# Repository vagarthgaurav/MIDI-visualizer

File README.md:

# MIDI Visualiser

by: Vagarth Gaurav and Maksim Eremenko

**Faculty of Technology and Bionics**

***Rhine-Waal University of Applied Sciences***

Date: 23 January 2024

----

## Abstract

The MIDI Visualiser implements an overarching idea of showing visual patterns on a rudimentary screen made of smart light-emitting diode (LED) strips based on the Musical Instrument Digital Interface (MIDI) keyboard output. The board design includes a buck-converter that steps down the power input voltage from 12v to 5v for the ATmega microcontroller unit (MCU), while also feeding the 12v to LED strips. MCU receives a MIDI input through a software serial, processes it and sends an output signal controlling an LED strip to display different patterns based on the pressed key. Out of curious ambition - prevalently SMD components were used, which ultimately led to a failed attempt to print at Hochschule Rhein-Waal (HSRW), instead the PCB was ordered from a third party. After arduous soldering, resoldering, coding and debugging the concept proved to be feasible. Although the prototype is working - further code optimization is necessary and additional ergonomic improvements should be considered.

## 1 Introduction

From the very dawn of Humankind our senses were the main gateway of perceiving and accepting the world around us. Throughout the social evolution of Homo sapiens, we've developed peculiar ways of stimulating our senses, ways that "make sense" only from a perspective of a conscious being with ears and sight. A marvelous play of stimulations to our hearing facilities that became known as music, and an intriguing play of visual symbols that found itself in different aspects of visual art and media. Consciously or not - our project stands among the attempts to unite and enhance an auditory sensation with a visual one.

At the end of the 20th century music entered the electronic era, synthesizers rose in popularity and MIDI was developed. Digital MIDI signals can be sent by any MIDI-compatibly musical instrument, such as keyboards, guitars and other more exotic contraptions. These signals contain information about the note being pressed or released, which can be processed by a 3rd party computing unit usually responsible for generating a corresponding sound, but in our case - responsible for generating visual patterns on an LED screen made of smart LED strips (further simply "LED screen").

LED screen therefore can dynamically respond to the notes being played, different animated patterns can be shown in different parts of the screen. Patterns can be colored and animated based on the press and release velocities creating an immersive supplementary experience to the music being played.

The following Chapter 2 presents our approach to implementing this idea, the hardware we designed and the software we wrote, as well as inevitable issues we've encountered.
Chapter 3 describes and illustrates the results, our success and our shortcomings. 
Finally, Chapter 4 will discuss the viability of our approach and potential improvements.

## 2	Methodology

### 2.1	Concept development

The initial concept was outlined in the following diagram:

A block diagram of an initial idea.

The following MIDI schematic depicts MIDI input and throughput isolated from the process control block (PCB) circuit via an opto-coupler.

Isolated MIDI IN and THRU.
(C) 1985 MIDI Manufacturers Association via https://diyaudiocircuits.com/midi-buffer/

Additionally, we already had a 12V 5A power source in our possession, so it was decided to design the solution around that power input.

From these, an idea of core circuit elements crystallized:
- A voltage regulator that can efficiently step down from 12V to 5V.
- MIDI input and throughput isolated from the circuit by means of an optocoupler.
- 5V ATmega328p MCU to read and interpret incoming MIDI signal.
- LED screen made of 3 rows of smart LED strips powered by 12V line.
- Performant software to bind MIDI input with visual LED screen output.
- Programmer pins
- Pins for power and auxiliary switches

### 2.2	Circuit design

The circuit was designed in KiCad

SMD components were selected wherever possible for their compact size and as a personal opportunity to discover SMD PCB manufacturing process.
As a voltage regulator - a buck convertor was used due to its high efficiency in comparison to archaic linear voltage regulators.

#### 2.2.1 Power regulator

Power regulator circuit

The device uses a buck converter to convert 12V to 5V necessary to power the MCU and other IC’s. The device used is ADP2303ARDZ-5.0 from Analog Devices. The circuit was designed in accordance with the typical application circuit from the datasheet. [1] 

#### 2.2.2 Microcontroller and crytal circuitry

Microcontroller and crystal circuitry

The microcontroller chosen is an ATmega328p-au. As datasheet 2 suggests the MCU requires a 16Mhz clock crystal. The MCU has associated decoupling capacitors of 1uF and a bulk decoupling capacitor of 10uF. The MIDI input signal is read in by the MCU at Pin PD5. The output for the LED data pin is assigned to Pin PB0. 

Prior to soldering the IC to the PCB the Arduino bootloader was uploaded with the use of a TQFP32 breakout board. This was necessary as an error in design was made by not including an ISP header for programming. The Arduino bootloader can only be uploaded with the MCU’s ISP pins. 

The program is uploaded to the PCB once it is completed with the help of an FTDI programmer. The PCB has pins broken out for plugging a programmer. 

#### 2.2.3 MIDI input

MIDI Input circuit

The MIDI signal is read in with the use of a MIDI socket. The signal is fed into an optocoupler for galvanic isolation to prevent ground loops. The signal then goes to the MCU for processing. 

#### 2.2.4 MIDI Thru

MIDI thru circuit

The MIDI thru circuit is fairly simple. A hex inverter IC is used with the signal passed through 2 inverters. This acts as a buffer for delivering a stable signal. 

### 2.3	Prototyping

The MIDI input circuitry was prototyped with a breadboard for a proof of concept. The circuit is the exact same as in the schematic with THT components. As expected the MIDI signal was successfully read. An Arduino Uno was used to read and process the signal. 

The power regulator circuit was also to be prototyped but unfortnately the ADP2303 is not available in a THT package and was therefore not possible. Nonetheless, since the Datasheet was very thorough and was implemented exactly according to specification this turned out to not be necessary after all. The power regulator in the final PCB outputs a steady 5V output as expected. 

### 2.4	Printing

The first attempt to print the KiCad design was made using HSRW electronics lab chemical PCB etching facilities.

Unfortunately, but not unexpectedly, due to the small width of SMD pads and traces (under 0.5mm) too many of the traces got destroyed during the etching process. As a result, it was decided to order an etched PCB from a 3rd party. Fortunately this time we received a perfect PCB that didn't require any manual alteration, so we were able to start the component soldering process.

### 2.5 Soldering

The soldering pipeline used involved a careful application of a limited amount of soldering paste to component pads using a soldering paste pump, followed by precise placement of SMD components using the magnetic pick-and-place machine. Afterwards, PCB was placed in a reflow oven which melted the paste effectively soldering the components in place. An initial attempt was not ideal, MCU came out of the oven with multiple pins short-circuited with melted solder. A cleanup attempt employing a soldering iron and a solder braid succeeded only partially. It was decided to desolder the MCU using the heat gun in the process of which the first PCB was destroyed.

PCB soldering was started from scratch using a fresh PCB and a new set of components, the same process was repeated, yet the second bake resulted in a resounding success with no short-circuits.

Following that thru-hole components (THC), such as MIDI ports, power jack and connector pins - were soldered. Subsequent connectivity tests showed that hardware functions as expected and opened a road ahead to software development and testing.

### 2.6 Software

Software was written using Arduino IDE as well as Visual Studio Code with an Arduino plugin.
The core idea behind the software was inspired by a style of image rendering employed by graphics processing unit (GPU) shaders. The software implements multiple crucial concepts:
- A screen, where every pixel is an LED addressable by an x and y coordinate.
- A shape that can have a specific size, position and color.
- A screen pixel that can sample every existing shape to determine its own color, potentially as a blend of colors of intersecting shapes.

The following libraries were used:

```c++
#include <MIDI.h>
#include <Adafruit_NeoPixel.h>
#include <Deneyap_RenkDonusturme.h>
```

Every main loop iteration - each screen pixel attempts to sample every existing shape, mix the colors of all the shapes it belong to (if any) and based on that conclude its own color:

```c++
Color pixelBrain(const AbsPosition &absPos, const RelPosition &relPos)
{    
    Color color = {0, 0, 0, 0};
    bool nocolor = true;

    // Loop through all the shape and sample every shape color. Returns 0 color if pixel doesnt belong to a shape.
    for (auto &shape : shapes)
    {
        if (shape.isActive())
        {
            // Sample color and mix it with a previously sampled color using alpha-blending
            auto c = shape.sampleColor(relPos);
            if (c.a != 0)
            {
                if (nocolor)
                {
                    color = c;
                    nocolor = false;
                }
                else
                {
                    color.a = lerp(color.a, 255, byteToFloat(c.a));
                }
            }
        }
    }

    // Return pixel color
    return color;
}
```

At the same time, MIDI input is listened to and in the event of a key press or release - a new shape is created or removed based on the note value in a way that leftmost keys generate shapes in the leftmost part of the screen, while rightmost - in the rightmost. The shape was meant to quickly fade in and gradually fade out when the key is released, although this approach was later altered.

The downside of this approach: each main loop iteration at worse does 3600 pixel iterations (60 pixels x 30 objects), initial assumption that MCU should be able to handle it at 120Hz of the main loop refresh rate - prooved to be false. At the full load, a significant slowdown is noticeable.

Additionally - the research suggests that limitations of ATmega memory make dynamic memory management highly undesirable due to possible rapid memory fragmentation leading to an inevitable silent crash. In response to that - everything, including shape instances, was preallocated, but due to the limited amount of memory (2kb) the hard limit of 30 simultaneous shapes on the screen was introduced.

Throughout the implementation testing, it became obvious that some of the MIDI events are simply missing. Through the following process of research and debugging it was discovered that the culprit might've been an initial ignorant decision to use a software serial pin instead of the hardware serial one, it appears that in a former case, some serial signals can be lost when MCU is busy with other work. 
If a shape disappearance depends on a MIDI note-off signal - then if such signal went missing - the shape will linger, which is visually noticeable and undoubtedly undesirable. Since we had no ability to reroute the MIDI trace to a hardware serial pin - the issue was worked around on the software side by listening only to note-on events that spawn the shape and fading out the shape after a set amount of time, this way it was possible to trade noticeable false positives for less noticeable false negatives.

## 5	Results

The final assembled PCB worked as intended. Uploading code with the FTDI programmer was successful. The MIDI signal was successfully read and processed by the MCU and the LED strip was illuminated with the correct animation. 

The only flaw in the design was the absence of an ISP header pins. This was crucial as the Arduino bootloader could not be installed on the MCU. As explained above an attempt was made to desolder the IC and to use a TQFP32 breakout board and to upload the bootloader. Unfortunately, the PCB and the MCU were damaged and had to start over with a fresh PCB.

The second attempt was successful and the PCB performed as intended.

The final PCB

## 6	Discussion

The goal of this project was to bring up a PCB that could decode a MIDI signal from an instrument and be able to play an animation on a Neopixel LED display. With this in mind, the project was a success. 

A few things that could have been optimized. The first being the use of Hardware serial instead of Software Serial. The software does not have sufficient speed and in consequence, dropped some of the MIDI messages. This could have been avoided by using Hardware Serial. Unfortunately, the Atmega328p-au has only one Serial port, which was already used for programming. Secondly, the code could have been optimized a lot. The current code unfortunately does not perform very well on the Atmega328p. The idea was for the code to be as robust as possible to be able to handle an LED display of any length. This proved to be too much for the MCU to handle. Code optimisation can improve the usability a lot. The third and final room for improvement is to upgrade the MCU entirely and use something that is faster and has a lot more RAM. An STM32 chip would be a massive improvement. An added benefit is more number of Serial ports. 

A comment on the issue of not including a ISP programming header as already mentioned before. The absence of which was a major downside, which was eventually solved but would have saved a lot of time and effort and would have added robustness to the board. In future designs the inclusion of ISP headers as well as a hardware debug port such as Serial wire debug would provide for a much more comfortable experience. 

The design was able to achieve all the requirements and functioned with only minor deficiencies that are easily fixable in a future iteration. 

Finally, the cost of the PCB was below the estimated €20 limit. Using only minimal components and allocating more budget to the most important parts worked out to a board that is capable of enhancing the music playing experience for less than €20. 

## 7	Concluding Comments

A future iteration of this design would certainly include the above-mentioned improvements as well as a few more user experience-enhancing aspects. A 3D printable case to fit the board would help in protecting the board. An Onboard LED array would be an added benefit that could make the device function independently without the need for an external LED strip display. A seamless switching between the onboard and external display by detecting if a display is plugged in would make the device a well-rounded product. 

It's also undoubtedly possible to refactor the code to drastically reduce the amount of per-loop iterations by iterating over the shapes and filling pixels, instead of iterating over pixels and sampling shapes. This approach will not result in any perceivable drawbacks, except of an arguable drawback of worse code architecture, but will most likely significantly increase performance.

The experience of going through the project was very enjoyable and rewarding. The opportunity to learn was immense and the knowledge gained from this can be certainly applied to future projects.

## 8	References

* [1] ADP2303 Datasheet - https://www.analog.com/media/en/technical-documentation/data-sheets/adp2302_2303.pdf
* [2] ATmega328p-au datasheet - https://www.mouser.de/datasheet/2/268/ATmega48A_PA_88A_PA_168A_PA_328_P_DS_DS40002061B-3050139.pdf

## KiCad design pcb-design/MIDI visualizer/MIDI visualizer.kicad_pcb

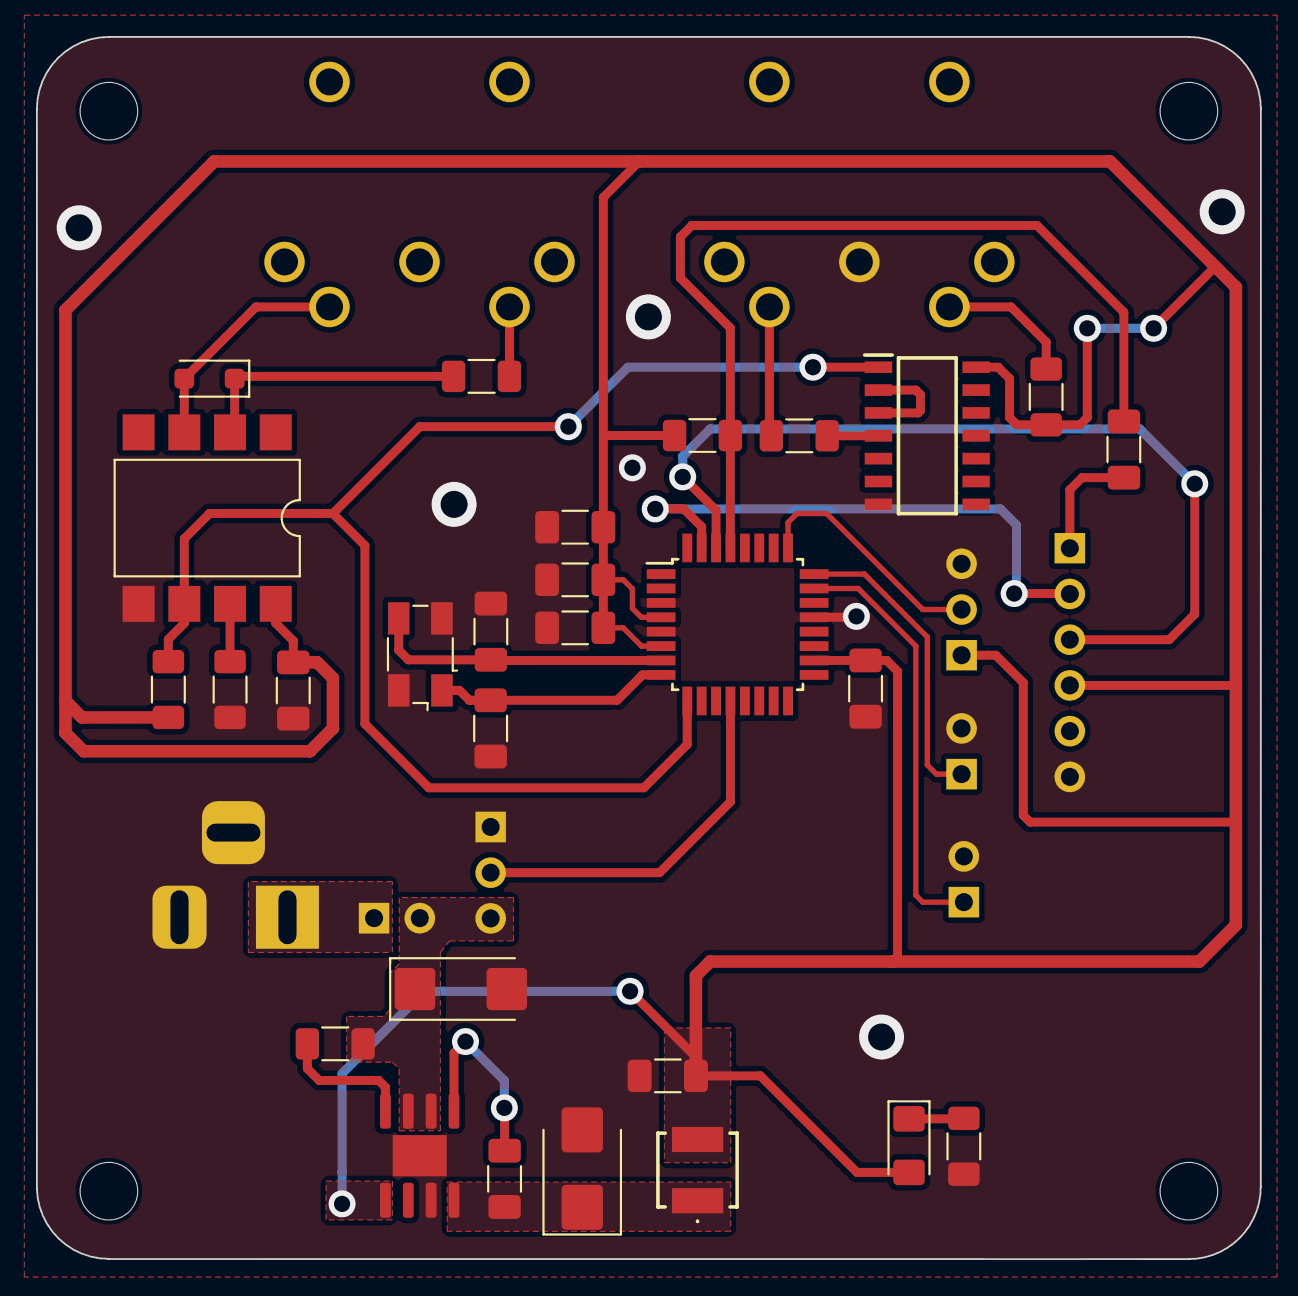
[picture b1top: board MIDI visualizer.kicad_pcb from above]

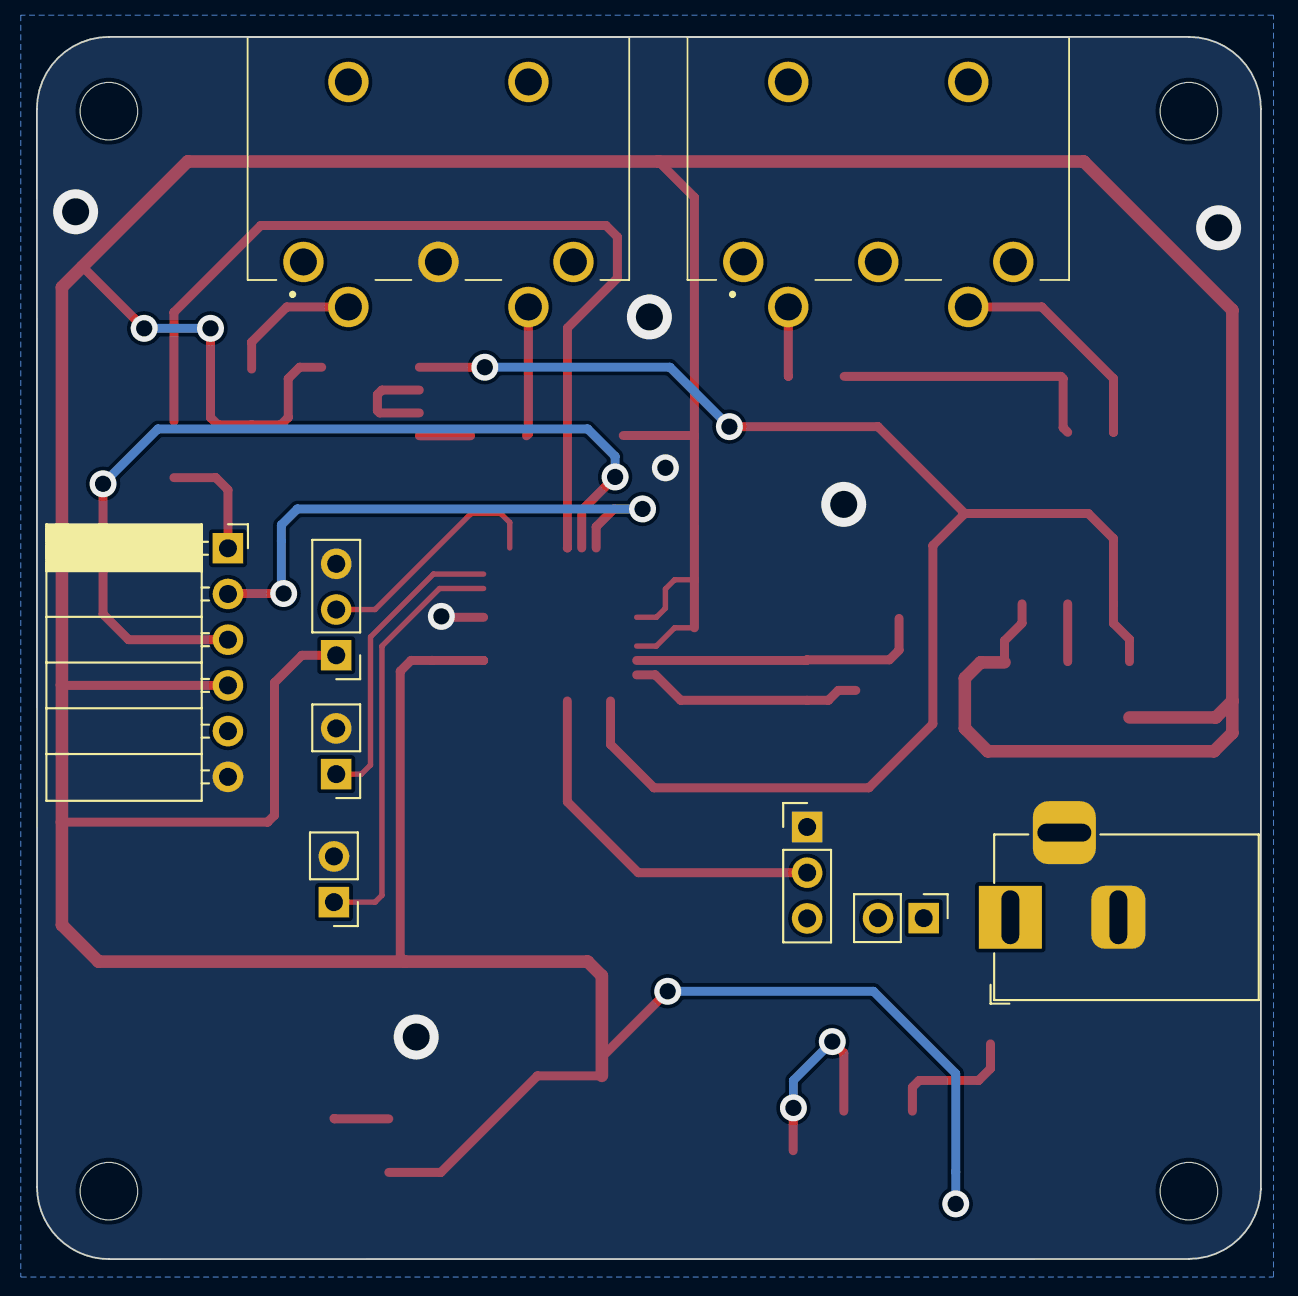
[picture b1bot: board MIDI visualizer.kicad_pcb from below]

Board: 2 copper layers, 68.0 x 67.9 mm, 41 parts (9 on the bottom side), 25 nets.

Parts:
C1: 10uF 25V; CP_EIA-6032-28_Kemet-C_Pad2.25x2.35mm_HandSolder
C2, C4, C10: 0.1uF; C_1206_3216Metric_Pad1.33x1.80mm_HandSolder
C3: 47uF 6.3V; C_1206_3216Metric_Pad1.33x1.80mm_HandSolder
C5: 10uF; C_1206_3216Metric_Pad1.33x1.80mm_HandSolder
C6, C7, C11: 1uF; C_1206_3216Metric_Pad1.33x1.80mm_HandSolder
C8, C9: 22pF; C_1206_3216Metric_Pad1.33x1.80mm_HandSolder
D1: SSB43L; D_SMB
D2: PWR_LED; LED_1206_3216Metric_Pad1.42x1.75mm_HandSolder
D3: 1N914; D_SOD-123F
H1, H2, H3, H4: MH; MountingHole_3.2mm_M3_DIN965
IC1: SN74HCT04DR; SOIC127P600X175-14N
J1: PWR Jack; BarrelJack_Horizontal
J2: locked; PinHeader_1x02_P2.54mm_Vertical
J3: MIDI Input; MIDI 5 pin jack
J4: MIDI Thru out; MIDI 5 pin jack
J5: Switch 1; PinHeader_1x02_P2.54mm_Vertical
J6: Switch 2; PinHeader_1x02_P2.54mm_Vertical
J7: 1K Pot; PinHeader_1x03_P2.54mm_Vertical
J9: LED connector; PinHeader_1x03_P2.54mm_Vertical
J10: UART; PinSocket_1x06_P2.54mm_Horizontal
L1: 4.7uH; SRP04154R7K
R1: 100k; R_1206_3216Metric_Pad1.30x1.75mm_HandSolder
R2: 100R; R_1206_3216Metric_Pad1.30x1.75mm_HandSolder
R3, R5, R6, R7: 220R; R_1206_3216Metric_Pad1.30x1.75mm_HandSolder
R4: 4.7k; R_1206_3216Metric_Pad1.30x1.75mm_HandSolder
R8: 10K; R_1206_3216Metric_Pad1.30x1.75mm_HandSolder
U1: Convertor ADP2303ARDZ-5.0; SOIC-8-1EP_3.9x4.9mm_P1.27mm_EP2.29x3mm
U2: 6N138 Optocoupler; SMDIP-8_W9.53mm
U3: ATmega328P-A; TQFP-32_7x7mm_P0.8mm
Y1: 16Mhz; Crystal_SMD_Abracon_ABM3B-4Pin_5.0x3.2mm

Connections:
+5V: C3.1, C4.2, C5.1, C6.1, C7.1, C11.1, D2.2 (A), IC1.14 (VCC), J7.1, J10.4, L1.2, R5.1, R6.1, R8.1, U1.5 (FB), U2.8 (VCC), U3.4 (VCC), U3.6 (VCC), U3.18 (AVCC)
+12V: C1.1, J1.1, J2.1, J2.2, J9.3, R1.1, U1.2 (Vin), U1.3 (EN)
/Anode: D3.1 (K), R3.1, U2.2 (C1)
/BST: C2.1, U1.1 (BST)
/CLOCK IN: C9.2, U3.7 (XTAL1/PB6), Y1.3
/CLOCK OUT: C8.1, U3.8 (XTAL2/PB7), Y1.1
/Cathode: D3.2 (A), J3.5, U2.3 (C2)
/MIDI THRU: IC1.4 (2Y), R7.1
/PGOOD: R1.2, U1.4 (PGOOD)
/SW: C2.2, D1.1 (K), L1.1, U1.8 (SW)
GND: C1.2, C3.2, C4.1, C5.2, C6.2, C7.2, C8.2, C9.1, C11.2, D1.2 (A), IC1.7 (GND), J1.2, J1.3 (MountPin), J4.2, J5.2, J6.2, J7.3, J9.1, J10.6, R2.2, R4.2, U1.7 (GND), U1.9 (PADGND), U2.5 (GND), U3.3 (GND), U3.5 (GND), U3.21 (GND), Y1.2, Y1.4
LED DATA: J9.2, U3.12 (PB0)
MIDI IN: IC1.1 (1A), R5.2, U2.6 (VO2), U3.9 (PD5)
unnamed: D2.1 (K), R2.1
unnamed: IC1.2 (1Y), IC1.3 (2A)
unnamed: J3.4, R3.2
unnamed: J4.4, R6.2
unnamed: J4.5, R7.2
unnamed: R4.1, U2.7 (VO1)
Pot: J7.2, U3.25 (PC2)
RESET: C10.1, C10.2, J10.1, R8.2, U3.29 (~RESET/PC6)
RX: J10.3, U3.30 (PD0)
SW1 In: J5.1, U3.23 (PC0)
SW2 In: J6.1, U3.24 (PC1)
TX: J10.2, U3.31 (PD1)

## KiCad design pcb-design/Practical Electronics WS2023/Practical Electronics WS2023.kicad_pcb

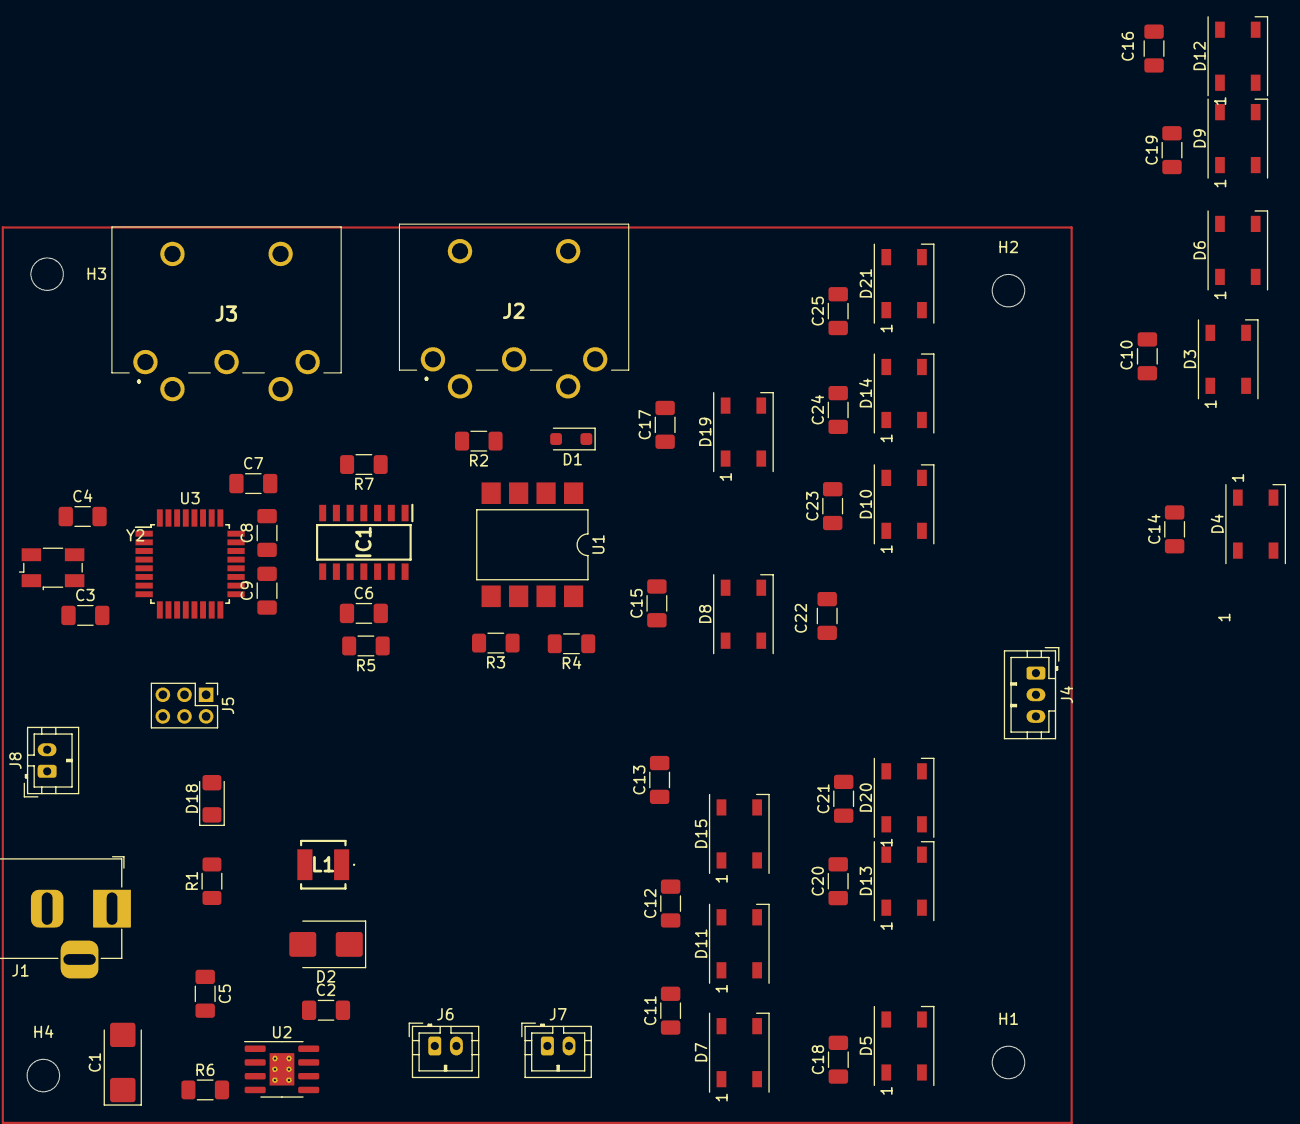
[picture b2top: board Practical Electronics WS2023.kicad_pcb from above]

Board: 2 copper layers, 69 parts (0 on the bottom side), 42 nets, no tracks yet.

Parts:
C1: 10uF 25V; CP_EIA-6032-28_Kemet-C_Pad2.25x2.35mm_HandSolder
C2, C6, C10, C11, C12, C13, C14, C15, C16, C17, C18, C19, C20, C21, C22, C23, C24, C25: 0.1uF; C_1206_3216Metric_Pad1.33x1.80mm_HandSolder
C3, C4: 22pF; C_1206_3216Metric_Pad1.33x1.80mm_HandSolder
C5: 47uF 6.3V; C_1206_3216Metric_Pad1.33x1.80mm_HandSolder
C7: 10uF; C_1206_3216Metric_Pad1.33x1.80mm_HandSolder
C8, C9: 1uF; C_1206_3216Metric_Pad1.33x1.80mm_HandSolder
D1: 1N914; D_SOD-123F
D2: SSB43L; D_SMB
D3, D4, D5, D6, D7, D8, D9, D10, D11, D12, D13, D14, D15, D19, D20, D21: WS2812B; LED_WS2812B_PLCC4_5.0x5.0mm_P3.2mm
D18: PWR_LED; LED_1206_3216Metric_Pad1.42x1.75mm_HandSolder
H1, H2, H3, H4: MountingHole; MountingHole_3mm
IC1: NOT GATES N74HCT04DR; SOIC127P600X175-14N
J1: PWR Jack; BarrelJack_Horizontal
J2: MIDI Input; MIDI 5 pin jack
J3: MIDI Thru out; MIDI 5 pin jack
J4: LED Connector Conn_01x03; JST_PH_B3B-PH-K_1x03_P2.00mm_Vertical
J5: ISP; PinHeader_2x03_P2.00mm_Vertical
J6, J7, J8: Switch connector; JST_PH_B2B-PH-K_1x02_P2.00mm_Vertical
L1: 4.7uH; SRP04154R7K
R1: 100R; R_1206_3216Metric_Pad1.30x1.75mm_HandSolder
R2, R4, R5, R7: 220R; R_1206_3216Metric_Pad1.30x1.75mm_HandSolder
R3: 4.7k; R_1206_3216Metric_Pad1.30x1.75mm_HandSolder
R6: 100k; R_1206_3216Metric_Pad1.30x1.75mm_HandSolder
U1: 6N138 Optocoupler; SMDIP-8_W9.53mm
U2: Convertor ADP2303ARDZ-5.0; SOIC-8-1EP_3.9x4.9mm_P1.27mm_EP2.29x3mm_ThermalVias
U3: ATmega328P-A; TQFP-32_7x7mm_P0.8mm
Y2: 16Mhz; Crystal_SMD_Abracon_ABM3B-4Pin_5.0x3.2mm

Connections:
+5V: C5.1, C6.2, C7.1, C8.1, C9.1, D18.2 (A), IC1.14 (VCC), J5.1, L1.2, R4.1, R5.1, U1.8 (VCC), U2.5 (FB), U3.4 (VCC), U3.6 (VCC), U3.18 (AVCC)
+12V: C1.1, C10.1, C11.1, C12.1, C13.1, C14.1, C15.1, C16.1, C17.1, C18.1, C19.1, C20.1, C21.1, C22.1, C23.1, C24.1, C25.1, D3.1 (VDD), D4.1 (VDD), D5.1 (VDD), D6.1 (VDD), D7.1 (VDD), D8.1 (VDD), D9.1 (VDD), D10.1 (VDD), D11.1 (VDD), D12.1 (VDD), D13.1 (VDD), D14.1 (VDD), D15.1 (VDD), D19.1 (VDD), D20.1 (VDD), D21.1 (VDD), J4.3, J8.1, R6.1, U2.2 (Vin), U2.3 (EN)
GND: C1.2, C3.2, C4.1, C5.2, C6.1, C7.2, C8.2, C9.2, C10.2, C11.2, C12.2, C13.2, C14.2, C15.2, C16.2, C17.2, C18.2, C19.2, C20.2, C21.2, C22.2, C23.2, C24.2, C25.2, D2.2 (A), D3.3 (VSS), D4.3 (VSS), D5.3 (VSS), D6.3 (VSS), D7.3 (VSS), D8.3 (VSS), D9.3 (VSS), D10.3 (VSS), D11.3 (VSS), D12.3 (VSS), D13.3 (VSS), D14.3 (VSS), D15.3 (VSS), D19.3 (VSS), D20.3 (VSS), D21.3 (VSS), IC1.7 (GND), J1.2, J3.2, J4.1, J5.2, J6.2, J7.2, R1.2, R3.2, U1.5 (GND), U2.7 (GND), U2.9 (PADGND), U3.3 (GND), U3.5 (GND), U3.21 (GND), Y2.2, Y2.4
LED DATA: J4.2, U3.13 (PB1)
MIDI IN: IC1.1 (1A), R4.2, U1.6 (VO2), U3.12 (PB0)
MISO: J5.4, U3.16 (PB4)
MOSI: J5.5, U3.15 (PB3)
unnamed: D1.2 (A), J2.5, U1.3 (C2)
unnamed: D1.1 (K), R2.1, U1.2 (C1)
unnamed: C2.2, D2.1 (K), L1.1, U2.8 (SW)
unnamed: D3.2 (DOUT), D6.4 (DIN)
unnamed: D4.2 (DOUT), D5.4 (DIN)
unnamed: D5.2 (DOUT), D7.4 (DIN)
unnamed: D6.2 (DOUT), D9.4 (DIN)
unnamed: D7.2 (DOUT), D8.4 (DIN)
unnamed: D8.2 (DOUT), D10.4 (DIN)
unnamed: D10.2 (DOUT), D11.4 (DIN)
unnamed: D11.2 (DOUT), D13.4 (DIN)
unnamed: D9.2 (DOUT), D12.4 (DIN)
unnamed: D12.2 (DOUT), D15.4 (DIN)
unnamed: D13.2 (DOUT), D14.4 (DIN)
unnamed: D15.2 (DOUT), D19.4 (DIN)
unnamed: D18.1 (K), R1.1
unnamed: D19.2 (DOUT), D20.4 (DIN)
unnamed: D20.2 (DOUT), D21.4 (DIN)
unnamed: IC1.2 (1Y), IC1.3 (2A)
unnamed: IC1.4 (2Y), R7.1
unnamed: J2.4, R2.2
unnamed: J3.4, R5.2
unnamed: J3.5, R7.2
unnamed: J6.1, U3.10 (PD6)
unnamed: J7.1, U3.11 (PD7)
unnamed: J1.1, J8.2
unnamed: R3.1, U1.7 (VO1)
unnamed: C2.1, U2.1 (BST)
unnamed: R6.2, U2.4 (PGOOD)
unnamed: C4.2, U3.7 (XTAL1/PB6), Y2.3
unnamed: C3.1, U3.8 (XTAL2/PB7), Y2.1
ONBOARD LED DATA: D3.4 (DIN), U3.30 (PD0)
R1_DOUT: D4.4 (DIN), D21.2 (DOUT)
RESET: J5.3, U3.29 (~RESET/PC6)
SCK: J5.6, U3.17 (PB5)

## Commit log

2021-09-28 Add example folders
2021-09-28 copy structure from word template
2021-09-28 work in progress
2021-09-28 Fix structure of the report
2021-09-28 add example image
2021-09-28 Refine the readme outline with image and code example
2021-09-28 Add table example
2022-09-29 add project idea and description placeholder
2022-09-29 example project idea
2022-10-04 Add presentation directory
2022-10-04 presentation files
2023-10-05 update project structure for WS2023
2023-10-08 Upload block diagram
2023-10-08 Update idea for project.
2023-10-08 Upload New File
2023-10-08 Update block diagram
2023-10-13 Filled out Project-description with a rough outline of component list.
2023-10-13 Fixed markdown
2023-10-13 Minor tweaks
2023-10-13 Added a potential regulator that might fit, for reference.
2023-10-13 Added info on capacitors for the linear regulator.
2023-10-14 More stuff
2023-10-20 buck convertor is a PITA
2023-10-20 Changed buck converter to simpler one
2023-10-22 Midi and voltage reg schematics
2023-10-22 Update schematic
2023-10-22 Rename file and add parts list
2023-10-22 Add PDF of schematic
2023-10-24 Replace MIDI Visualiser.kicad_sch
2023-10-24 Replace MIDI Visualiser.pdf
2023-10-29 Updated list of components
2023-10-30 Create PCB project
2023-10-31 Update voltage regulator
2023-11-03 Power switch, logic switches, LED strip detection, onboard LEDs are 2x8.
2023-11-03 Updated switches to match toggle switch pin configurations
2023-11-05 removed led detector
2023-11-05 The list of components, WIP
2023-11-05 replaced sitches with switch connectors
2023-11-05 most of the footprints assigned
2023-11-05 footprints
2023-11-06 Preliminary board layout
2023-11-06 Prototyping parts list
2023-11-07 PCB WIP
2023-11-13 Archive old project
2023-11-13 Create new project
2023-11-14 basic traces
2023-11-17 Update pcb
2023-11-19 Rendered pdf
2023-11-20 Polish board
2024-01-04 Core software implementation
2024-01-05 Arduino was freezing due to going out of memory, made the source of error more obvious, screen.h needs to be refactored to an extent, we can not store pixel indices, they require too much space.
2024-01-05 Cleanup
2024-01-05 More Cleanup
2024-01-05 Working (allegedly) implementation. Only need to add LED library and send calculated colors to calculated led indices
2024-01-05 simplified shape config
2024-01-14 Software version that ctually works
2024-01-15 Presentation pdf
2024-01-23 Report WIP
2024-01-23 Report header
2024-01-23 report suggestions
2024-01-23 Added schematic and results
2024-01-23 Added discussion and concluding comments
2024-01-23 probably a final version of the report
2024-01-23 fixed schematic file name
2024-01-23 fixing image description
2024-01-23 Almost certain that this is a final version
2024-01-23 Now this is final.
